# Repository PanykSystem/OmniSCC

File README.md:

# OmniSCC — MSX MultiCart

Current firmware: **2.0.0**. See [release notes — changes since 1.0.0](RELEASE_NOTES.md).

> **Upgrading from 1.0.0:** back up every file on the cartridge before flashing.
> This release changes the flash layout and automatically formats a recognized
> old volume on its first boot. Restore your files afterwards. Install the new
> UF2 and menu ROM together; older menu signatures are no longer recognized.

OmniSCC is an RP2040-based MSX cartridge that loads ROM and floppy disk images
from the Pico's 16 MB flash. It emulates plain and mapped ROM cartridges, the
Konami SCC sound chip, and floppy drives backed by `.dsk` files.

**ROM-game saves:** KUC supports flash saves in a companion `.sav`
for ROMs explicitly named with `[KUC]`, on compatible 16 MiB SPI NOR hardware.
See [KUC setup, capacity and validation status](src/docs/kuc.md).
For an unknown flash profile, both menus accept `kuc_allow_unknown_flash=1`
(default `0`); the hardware requirements still apply. Other cartridge flash,
SRAM and EEPROM profiles remain unsupported. Writable `.dsk` games continue to
save into their disk image.

When powered from USB without the MSX, it appears as a removable drive for
copying images by drag-and-drop. On the MSX, the universal menu browses
files and folders and remembers the last booted image. It automatically uses
SCREEN 1 on MSX1 and SCREEN 5 on recognized MSX2+ BIOS versions with enough VRAM. An alternative menu
provides ten configurable favourites.

*OmniSCC — a 16 MB "purple" Pico clone soldered directly onto the carrier
board.*

---

## Contents of this repository

| Path | What it is |
|------|------------|
| [`firmware/`](firmware/) | Prebuilt firmware images. |
| [`tools/`](tools/) | Menu ROMs, and MSX-DOS utilities. |
| [`src/`](src/) | RP2040 firmware (C11 / C++17) + the Z80 side (`msx/preloader.asm`, `msx/loader.asm`, `msx/loader_fav.asm`). See [`src/README.md`](src/README.md). |
| [`board/OmniSCC/`](board/OmniSCC/) | KiCad project for the base board: schematic, PCB, 3D STEP, fabrication ZIP. |
| [`board/OmniSCC+/`](board/OmniSCC+/) | KiCad project for the level-shifted board. |
| [`enclosure/`](enclosure/) | Printable 3MF files for the base and OmniSCC+ cases. |
| [`images/`](images/) | Board photos used by this file. |

Two software git submodules are used, so clone with:

```bash
git clone --recursive https://github.com/RBSC/OmniSCC.git
# or, in an existing clone:
git submodule update --init --recursive
```

---

## Hardware variants

Both boards run the same firmware sources; they differ only in the board header
selected at build time (`-DPICO_BOARD=omniscc` or `omniscc_plus`).

### OmniSCC (base)

*The Pico module is soldered flat against the carrier board along both pin
rows.*

The Pico drives the MSX bus directly at 3.3 V. Fewest parts, lowest cost. Three
3-pole solder jumpers pick what reaches the Pico on GP26–GP28:

| Jumper | Choice | Required setting for this firmware |
|--------|--------|------------------------------------|
| `IORQ` / `AUDIO` | GP26 | **AUDIO** — GP26 is the SCC PDM audio output. |
| `BUSDIR` / `M1` | GP27 | **BUSDIR** — the firmware never reads `/M1`. |
| `WAIT` / `INT` | GP28 | **WAIT** — the loader stretches every bus cycle with `/WAIT`. |

### OmniSCC+

*OmniSCC+ — same Pico module, plus SN74LVC8T245 bus transceivers for
proper 5 V level translation.*

Address, data and control lines run through level shifters, so the MSX sees
real 5 V logic. There are no option jumpers: GP26 is AUDIO, GP27 is the data
transceiver direction (`DATA_DIR`), GP28 is `/WAIT`. Build with
`-DPICO_BOARD=omniscc_plus`, which defines `WITH_SHIFTERS`.

---

Current [OmniSCC+ hardware revision 1.1](board/OmniSCC+/README.md) adds a
10 kΩ pull-up on `/RES` to address resets in USB mode when touching the connector.
Use the 1.1 fabrication archive for new boards.

## Quick start

1. **Flash the firmware.** Hold **BOOTSEL**, plug into USB, release; copy a
   `.uf2` to the `RPI-RP2` drive. Pre-built images live in
   [`firmware/`](firmware/) — `OmniSCC.uf2` for the base board,
   `OmniSCC+.uf2` for OmniSCC+. To build your own, see
   [`src/README.md`](src/README.md).
2. **Fill the drive.** Plug the cart into USB with the MSX powered off. A
   removable drive named `OmniSCC` appears (the first boot formats the flash and
   writes `WELCOME.TXT`). Copy [`tools/loader.rom`](tools/loader.rom)
   and your `.rom` files to its root. Keep only one `loader*.rom` in the root. To build the menu yourself, see
   [`src/README.md`](src/README.md).
3. **Nothing to configure.** The menu lists what is on the drive and writes
   `/loader.ini` itself when you boot something. Write it by hand only to set a
   countdown or a title before the first boot:

   ```ini
   delay=3000
   scc_on_exit=1
   scc_volume=100
   name=gradius.rom,Gradius
   ```

   For the ten-favourites menu, copy
   [`tools/loader_fav.rom`](tools/loader_fav.rom) to the drive
   **under its original name**. Copy `loader_fav.ini.example` to the drive as
   `loader_fav.ini`, then edit its `favN=` entries to match your files.
   Keep only one `loader*.rom` in the root; see
   [`src/README.md`](src/README.md#which-menu-rom-to-copy).
4. **Eject, plug into the MSX, power on.** The menu appears; it auto-boots
   whatever you booted last when the countdown runs out.

### Menu keys

| Key | Action |
|-----|--------|
| Cursor up / down | Move the highlight; the list scrolls at the edges |
| Cursor left / right | Page up / page down |
| `RETURN` / `SPACE` | Enter a directory, or boot a file |
| `F1` | Open Help, including the running firmware version |
| `BS` | Up one directory |
| `INS` | Assign the highlighted `.dsk` to drive B; pressing INS again keeps it assigned |
| `DEL` | Clear drive B, regardless of the selected entry |
| `ESC` | Leave the menu for BASIC (maps a bare SCC cartridge first if `scc_on_exit` is non-zero) |

Keyboard input or either joystick port cancels the auto-boot countdown.
Joystick directions navigate, A opens/boots, and B goes back or exits.

### SCC volume

The firmware and menus support a global SCC master level in
`loader.ini` (browser) or `loader_fav.ini` (favourites):

```ini
scc_volume=100
```

Use a decimal percentage from `0` to `100`. The default is `100`, which keeps
the previous output level; `50` halves the signal amplitude and `0` mutes SCC.
This is a linear amplitude control, so half the value need not sound half as
loud. The MSX's built-in PSG is unaffected. Channel volumes programmed by the
game keep their relative levels.

The setting applies to SCC ROM games, disk/Nextor SCC audio and the bare SCC
mode selected on exit. It survives SCC chip resets and cartridge changes.
Each menu reads its own INI at startup; restart the menu after editing it.
Invalid or out-of-range values leave the previous value (initially `100`)
unchanged. The browser preserves the setting when rewriting `loader.ini`;
the favourites menu preserves the other lines when saving volume and `default=`.
Install the matching UF2 and updated menu ROM together to use this option.

In either menu, press **`+` / `-`** to change the level in **10% steps**,
clamped to 0–100%. A centred `SCC Volume: 100%` popup appears only while
adjusting, then disappears after about two seconds. ESC dismisses the popup;
press ESC again to leave the menu. Other navigation keys dismiss it and work
normally. Any adjustment cancels auto-boot. The setting is saved when you boot
an entry or leave the menu (and whenever the browser otherwise saves its INI),
not on every keypress. In favourites, literal `-` now controls volume instead
of acting as the AZERTY shortcut for slot 6; the digit `6` still selects it.

### Floppy drive emulation

The cartridge serves `.dsk` files on its USB volume as floppy drives to the
MSX. Select an image in the browser menu to mount it as drive A; the MSX then
resets and boots through the emulated Disk ROM. Press `INS` on another `.dsk`
first to put it in drive B; `DEL` clears B regardless of the selection. The browser saves that choice as `disk2=` in
`loader.ini`. A diskette icon at the left of the row marks the image assigned to B:.
After INS/DEL, drive B status temporarily replaces the centered F1 Help /
Return Open hint. The next keyboard or joystick input restores the hint. Only folders and the assigned B: image have icons;
ordinary ROM and DSK files use the same plain rows in both modes.
You can also set `disk2=` by hand. Whether B: appears to the MSX
depends on the Disk ROM's own drive count; some dumps advertise only A:.

You must supply your own **16 KB MSX Disk ROM dump**; none is distributed with
this project. Copy it to the USB volume as `disk.rom`, or set `diskrom=<path>`
in `loader.ini` to use a different file. The firmware patches a copy of the
dump in RAM when mounting a disk and leaves the file untouched. A dump must
pass the firmware's validation, so an arbitrary 16 KB ROM will not work.
The following 16 KiB dumps have been tested. External downloads are available
from File-Hunter; verify the MD5 checksum before use:

- [yis805-128r2_disk.rom](https://download.file-hunter.com/System%20ROMs/machines/yamaha/yis805-128r2_disk.rom) — MD5: `814aad415b58cc3f78c7b571512b2006`
- [NATIONALDISK.rom](https://download.file-hunter.com/System%20ROMs/machines/yamaha/NATIONALDISK.rom) — MD5: `86269da485e852d9f581ac27f4ba32ff`

If disk games fail or glitch when another disk interface is installed, see
[freeing RAM with DEL during disk boot](#disk-games-fail-when-other-disk-interfaces-are-present).

Images are **writable**: MSX-DOS and Disk BASIC can save files directly into
the `.dsk` on the cartridge's flash. Set an image file's read-only attribute
on the USB volume to make the emulated disk write protected. `CALL FORMAT`
initializes a 360 KB or 720 KB image on either drive. SCC audio remains
available while a disk is mounted.

The firmware accepts any non-empty image whose size is a multiple of 512
bytes; it does not validate the disk's filesystem or geometry when mounting.
Standard 360 KB and 720 KB images work with the supported Disk ROMs. Other
sizes may mount, but Disk BASIC or MSX-DOS may fail when reading them, and
`CALL FORMAT` supports only the two standard sizes.

After booting a disk, you can change images without rebooting. For example,
`CALL OMOUNT("B:SIDE-B.DSK")` inserts an image into drive B and `CALL OEJECT("B:")`
removes it. `CALL ODISK` reports both drives; `CALL ODIR("GAMES")` lists disk
images on the cartridge's USB volume.

The same outer-volume also supports file management from BASIC:

```basic
CALL ODEL("OLD.DSK")
CALL OCOPY("SOURCE.DSK","BACKUP.DSK")
CALL ONEW("EMPTY.DSK")           ' 720 KiB formatted FAT12 image
CALL ONEW("SINGLE.DSK",360)      ' 360 KiB formatted FAT12 image
```

`ODEL` refuses an image mounted in drive A or B. `OCOPY` and `ONEW` never
overwrite an existing file, and copy transfers preserve every source sector.
New images are empty FAT12 images and are not mounted automatically. Paths are
literal `.dsk` paths on the cartridge volume; subdirectories and spaces are
supported.

The firmware unifies BASIC and DOS command names with the `O` prefix.
The old names are replaced. `tools/OmniSCC.dsk` includes all seven commands
and standard MSX-DOS 1.03 / COMMAND 1.11, requiring 64 KiB RAM.
See [disk contents and system-file provenance](tools/DOS-SYSTEM.md).

The matching MSX-DOS programs are `OMOUNT.COM`, `OEJECT.COM`, `ODISK.COM`,
`ODIR.COM`, `ODEL.COM`, `OCOPY.COM` and `ONEW.COM`; copy them into a DOS image
before use. See the [Disk BASIC command guide](src/README.md#disk-commands-from-basic)
and [MSX-DOS command guide](src/msx/dos/README.md) for syntax, protocol limits
and error handling.

---

Numbered DSK switching uses a held top-row digit `1–9` when the game next
accesses the disk BIOS. Press the game's own disk-check key while holding the
digit. Set `multidisk=0` in `loader.ini` or `loader_fav.ini` to disable it
(default `1`), for example if the game uses digits for its controls.

## Supported mappers

Detected automatically from the ROM contents: plain/linear, Konami (8 KB
pages), Konami SCC, ASCII8, ASCII16. Detection can be overridden by putting
`[Plain]`, `[8kB]`, `[Konami]`, `[KonamiSCC]`, `[SCCI]`, `[SCCPlus]`, `[ASCII8]`, `[ASCII16]` or `[KUC]` in the filename
before the extension. KUC supports up to 8 MiB and can also be selected by a known external database
hash.

Plain/Mirrored ROMs choose their start address from the ROM header, including
48 KiB images starting at `0000h`. `[Normal]` disables mirroring; `[0x0000]`,
`[0x4000]` and `[0x8000]` explicitly select a non-mirrored start address.
`[Mirrored4000]` fixes a mirrored ROM at `4000h`. Generic `[8kB]` is selected
by filename or database and switches all four 8 KiB windows, including `4000h`.
It is distinct from Konami and ASCII8; the instruction heuristic does not select it.

`[SCCI]` and `[SCCPlus]` emulate an expanded 128 KiB SCC-I RAM cartridge.
SCCI starts in compatible SCC mode; SCCPlus starts in enhanced mode for ROM
conversions using `B800h`. `[SCC+]` is an alias for `[SCCPlus]`. Both support
RAM-write modes and the `BFFEh`/`BFFFh` mode register. The ROM image initializes
cartridge RAM, with the unused space filled with `FFh`; changes are volatile.
These types are selected by tag or database, not by the instruction heuristic.

The SCC is emulated on core 1 and rendered as a PDM stream through PIO + DMA on
GPIO 26. A bare SCC cartridge with no ROM can also be mapped from the menu (just 
exit to basic), for software that expects an SCC to be present but supplies its 
own code.

ROMs up to 128 KiB are cached in RAM; larger ones are read directly from their
verified flash pages, without a permanent second copy. Mapper limits are Plain
64 KiB, Konami 256 KiB, Konami SCC 2 MiB, SCC-I/SCCPlus 128 KiB, ASCII8 2 MiB, ASCII16 4 MiB and explicit KUC 8 MiB.
The FAT storage area occupies 15 MiB, less flash-translation overhead.

## Nextor on the shared USB volume

Copy `tools/nextor.rom`, `tools/NEXTOR.SYS` and `tools/COMMAND2.COM` to the
cartridge root, then select `nextor.rom` in the menu. Nextor uses the existing
FAT12/FAT16 volume directly; no HDD image or repartitioning is required.
DOS2 needs at least 128 KiB of mapped MSX RAM. See the
[Nextor guide](src/docs/nextor.md), including `SET EXPERT ON` for COM programs.
The kernel and DOS files are distributed with [their licence](tools/NEXTOR-LICENSE.md).

## Storage recovery

If flash mapping is valid but FAT cannot mount, the cartridge starts USB MSC
for repair or formatting. Connect through USB, repair the existing filesystem
or format FAT12/FAT16, safely eject and restart. Files are not automatically
erased merely because FAT failed to mount.

A damaged or unrecognized flash map is recreated automatically with a fresh
FAT. **That reset loses the previous files.** If flash itself fails, USB still
enumerates but the storage remains not-ready. Install the matching firmware and menu ROM together.

## MSX1 and MSX2 menus

The 16 KiB universal `tools/loader.rom` includes a 32×24 SCREEN 1 interface with
the existing 8×8 font, rounded frame, folder and assigned-disk icons and inverse
selection. It retains the full browser functionality and 16 visible entries.
MSX1 or unknown BIOS versions select this interface; recognized MSX2+ BIOS
versions use SCREEN 5 only after a restoring probe confirms at least 32 KiB VRAM.
A V9938 by itself does not imply MSX2 BIOS or enough VRAM. No separate lite ROM
is required. The optional 16 KiB favourites menu uses the same automatic mode selection, font,
frame and inverse selection, with all ten slots, digit shortcuts, Help and auto-boot.

Both graphical menus show only the centered OmniSCC logo, without a menu subtitle,
while reading configuration
and preparing the menu. With at least 64 KiB VRAM, initialization uses a hidden
page and reveals the completed menu without a partial redraw. The splash adds
no fixed delay; MSX1 text mode and 32 KiB graphics retain the hidden-screen startup.

**Browser — MSX1 (SCREEN 1)**

**Browser — MSX2 (SCREEN 5)**

**Favourites — MSX1 (SCREEN 1)**

**Favourites — MSX2 (SCREEN 5)**

Menu mapper detection uses the exact eight bytes `OmniSCC\0` at ROM offset
`0x10`, independently of the filename. Explicit mapper tags retain priority.
The preloader still searches the root for the first `loader*.rom`; keep only
one such file. Verify release payloads with `sha256sum -c SHA256SUMS` from the
repository root.

---

## ROM mapper database

Copy `tools/romdb.bin` to the cartridge root with the matching menus. Both INI
files accept `romdb=/romdb.bin`; an empty value disables lookup. Filename tags
win, then known hashes, then the instruction heuristic. Matched tags are hidden
in both menus. See [database generation and custom hashes](src/docs/rom-database.md).

## Troubleshooting

### Older SCC+ ROM conversions hang or play only PSG

Select enhanced SCC+ mode with `[SCCPlus]` or `[SCC+]` in the filename; `[SCCI]`
starts in compatible SCC mode. Some older Konami Game Collection conversions
also contain loader bugs: bank switching with Z80 interrupts enabled, or reliance
on Disk ROM RAM-slot variables before those variables have been initialized.
Such images can work in one emulator configuration and fail on another machine
or boot differently after a reset.

Use a corrected conversion if the mapper is selected correctly but the game
still hangs or its music fails. The
[conversion loader fixes](https://www.msx.org/forum/msx-talk/general-discussion/konami-game-collection-roms-patches)
describe these issues. Changing SCC volume does not repair the game's loader.

### Disk games fail when other disk interfaces are present

Each initialized Disk ROM can reserve MSX RAM for its drives and disk buffers.
If the machine already has another Disk ROM and drives, adding OmniSCC's disk
interface can sharply reduce free RAM. A disk game may then fail to start,
hang or behave incorrectly even though the same image works with fewer disk
interfaces.

On computers with built-in disk drives, try holding **CTRL** immediately after
starting a DSK image in the OmniSCC menu. Keep it held through the restart and
initial disk boot. On Disk ROMs that support this option, CTRL disables the
second logical floppy drive and reduces disk-buffer memory usage, leaving more
RAM for the game. The effect depends on the machine and Disk ROM.

For the supported **Yamaha YIS805 Disk ROM** (`yis805-128r2_disk.rom`),
use the following boot procedure:

1. Select the `.dsk` image in the OmniSCC menu.
2. Press **Enter**, then immediately press and hold **CTRL**.
3. Keep **CTRL held until the game has finished loading**.

Hold CTRL during the restart and disk boot, not just while the menu is visible.
This is a Disk ROM boot option; its behavior can differ with another Disk ROM
or machine.

On some models, holding **DEL** during startup disables the built-in network
BIOS and can free additional RAM for disk games. This is a separate,
machine-specific boot option.

### ROM games fail after a warm reset

If a ROM game does not start from the OmniSCC menu after a reset, switch the
computer off for **at least 10 seconds**, then switch it on and try again.
A warm reset may leave RAM or peripheral state that affects the next launch;
a full power cycle gives the machine and cartridge a fresh startup.

---

## Enclosure

[`enclosure/`](enclosure/) contains ready-to-print `OmniSCC.3MF` (base board)
and `OmniSCC+.3mf` (level-shifted board). `carts.3mf` is also
included.
Fill free to remove non required parts in the slicer.

---

## Documentation

- [`src/README.md`](src/README.md) — building, flashing, `loader.ini`
  reference, mapper tags, troubleshooting.
- [`src/docs/omniscc_api.md`](src/docs/omniscc_api.md) — the Z80↔Pico
  command protocol, for writing your own MSX-side software.

---

## IMPORTANT!
The RBSC provides all the files and information for free, without any liability. 
The provided information, software or hardware must not be used for commercial purposes unless permitted by the RBSC.
Producing a small amount of bare boards for personal projects and selling the rest of the batch is allowed without the permission of RBSC.
When the sources of the tools are used to create alternative projects, please always mention the original source and the copyright!

---

## Contact information

The members of RBSC group Tnt23, Wierzbowsky, Pyhesty, Ptero, GreyWolf, SuperMax, VWarlock, ALSP and DJS3000 can be
contacted via the group's e-mail address:

info@rbsc.su

The group's coordinator could be reached via this e-mail address:

admin@rbsc.su

The group's website can be found here:

https://rbsc.su/
https://rbsc.su/ru

The RBSC's hardware repository can be found here:

https://github.com/rbsc

The RBSC's 3D model repository can be found here:

https://www.thingiverse.com/groups/rbsc/things

-= ! MSX FOREVER ! =-

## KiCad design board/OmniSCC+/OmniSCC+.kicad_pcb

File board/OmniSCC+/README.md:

# OmniSCC+ — level-shifted board

KiCad 8 project for OmniSCC+: the same 16 MB Raspberry Pi Pico clone, but with
SN74LVC8T245 bus transceivers between the RP2040 and the MSX slot, so the MSX
sees proper 5 V logic levels on the address, data and control lines.

## Revision 1.1

R7 (10 kΩ, 0805) pulls `/RES` up to `+5VA`. This hardware change addresses
spontaneous resets observed in USB mode when touching the connector on revision
1.0. Use the revision 1.1 PCB and fabrication archive for new boards.

## USB stability fix for revision 1.0

Revision 1.0 has no pull-up resistor on `/RES`. The floating reset signal can
cause spontaneous resets in USB mode, for example when touching the USB
connector. Add a **10 kΩ resistor between `/RES` and `+5VA`** to retrofit the
pull-up included as R7 on revision 1.1.

1. Disconnect the board from both the MSX and USB before soldering.
2. With the board oriented as in the picture, solder the 10 kΩ resistor and
   connecting wire between the two marked points. The resistor has no polarity.
3. Insulate the resistor lead and wire where needed so they cannot short to
   neighbouring pads or the cartridge edge contacts. Check the solder joints
   and reconnect USB to verify stable operation.

This is a hardware modification; changing the firmware alone does not add the
pull-up. Revision 1.1 already includes R7 and needs no additional resistor.

## Files

| File | Contents |
|------|----------|
| `OmniSCC+.kicad_sch` / `.kicad_pcb` / `.kicad_pro` | Schematic, layout, project |
| `production/OmniSCCplus_1_1_Gerber.zip` | Revision 1.1 Gerbers and drill files (no BOM/CPL) |
| `production/netlist.ipc` | Revision 1.1 IPC-D-356 netlist for electrical test |
| `fabrication-toolkit-options.json` | KiCad Fabrication Toolkit settings used to generate the ZIP |
| `Datasheets/OmniSCC+-v1.0-schematic.pdf` | Historical revision 1.0 schematic; use the KiCad schematic for 1.1 |
| `Datasheets/RPPICOPURPLE-pin-1024x438.jpg` | Pinout of the 16 MB Pico clone |
| `../../LICENSE` | Project license |

The old `production/OmniSCCplus_1_0_Gerber.zip` and `production/v1.0/` assembly
CSVs are retained for revision 1.0 only. They must not be used to assemble 1.1:
component positions changed and R7 was added. Generate new assembly exports
from the revision 1.1 KiCad project when needed.

Symbols and footprints come from the OSPC library
([OSPC_Library](https://github.com/VWarlock/OSPC_Library)); configure it before
opening the project.

## Differences from the base board

- Level shifters on the whole bus instead of a direct 3.3 V connection.
- No option jumpers. GP26 is `AUDIO`, GP27 is the data transceiver direction
  (`DATA_DIR`), GP28 is `/WAIT`. `/IORQ`, `/BUSDIR`, `/M1` and `/INT` are not
  routed to the RP2040.

Build the firmware for this board with `-DPICO_BOARD=omniscc_plus`, which
defines `WITH_SHIFTERS`.

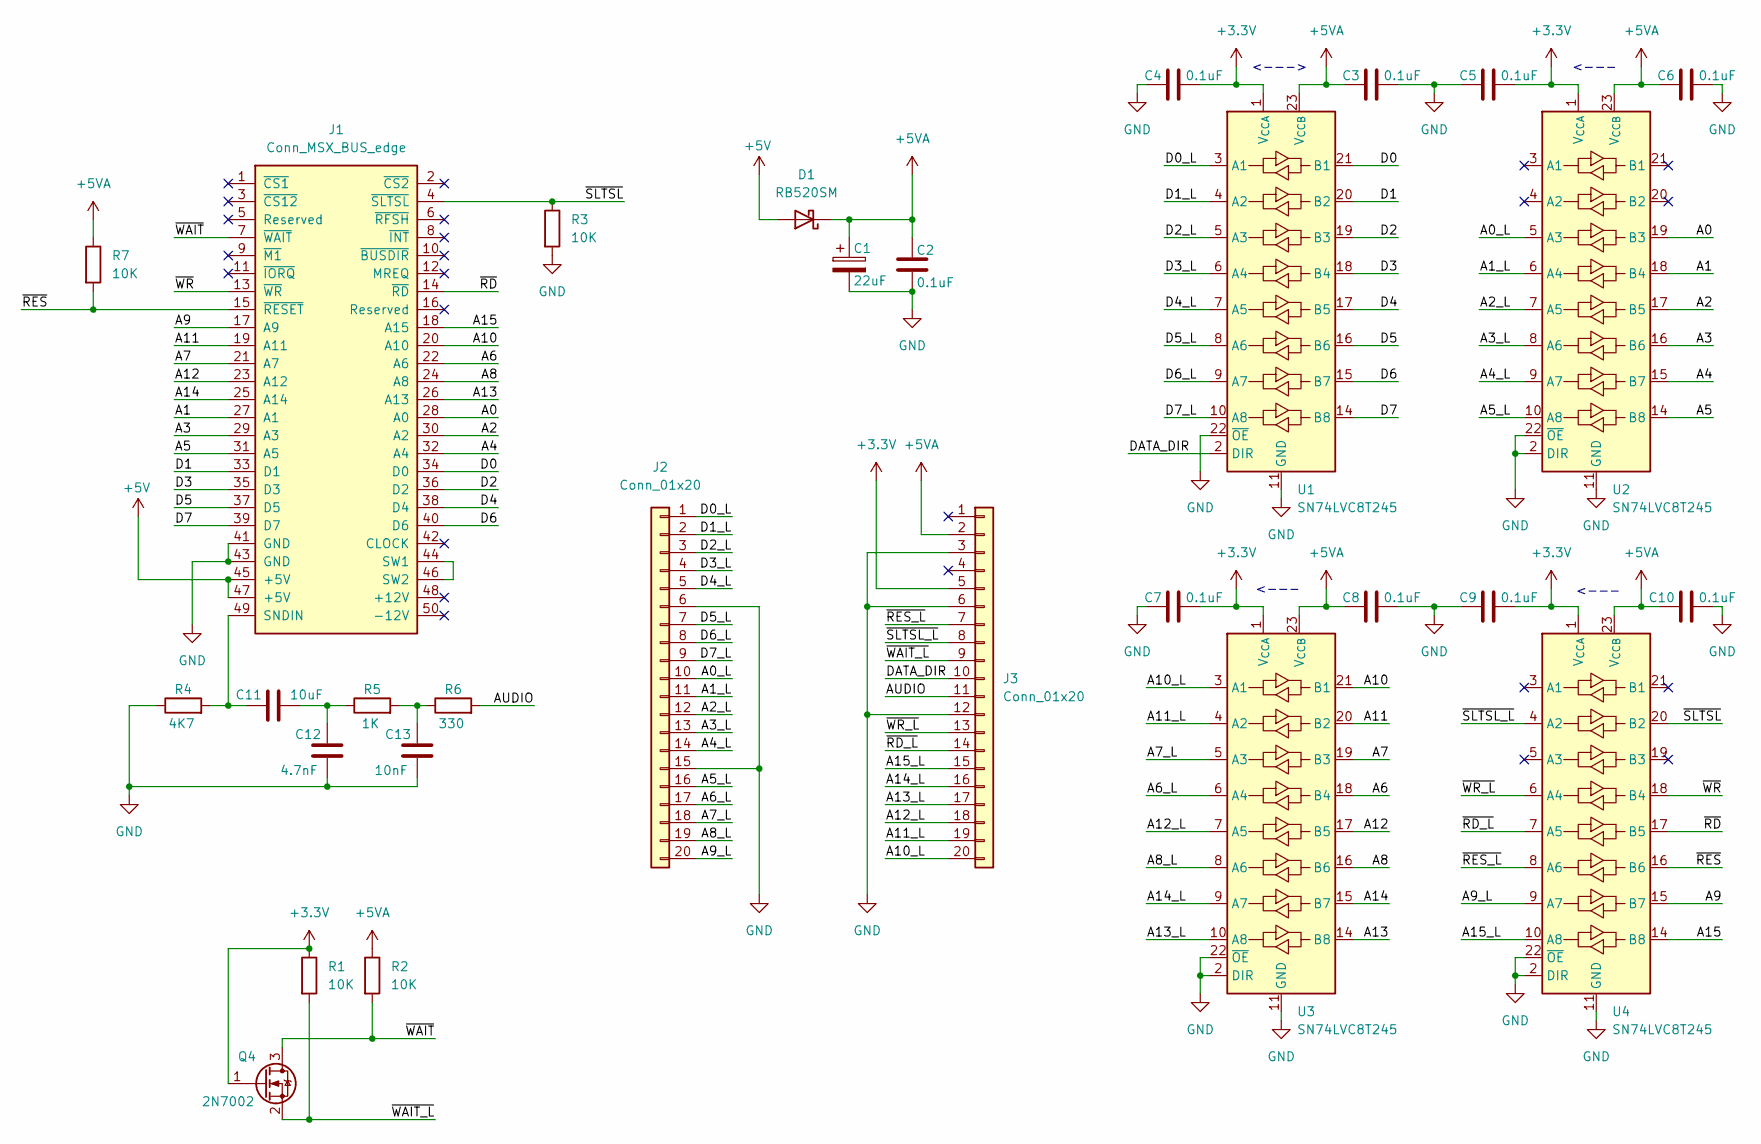
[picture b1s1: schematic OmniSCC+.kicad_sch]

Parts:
C1: 22uF; CP_EIA-3528-21_Kemet-B
C2, C3, C4, C5, C6, C7, C8, C9, C10: 0.1uF; C_0805_2012Metric
C11: 10uF; C_0805_2012Metric
C12: 4.7nF; C_0805_2012Metric
C13: 10nF; C_0805_2012Metric
D1: RB520SM; D_SOD-123; JLCPCB C8523
J1: Conn_MSX_BUS_edge; MSX_CART_SW_Small
J2, J3: Conn_01x20; PinSocket_1x20_P2.54mm_Vertical
Q4: 2N7002; SOT-23; LCSC C8545
R1, R2, R3, R7: 10K; R_0805_2012Metric_Pad1.20x1.40mm_HandSolder
R4: 4K7; R_0805_2012Metric
R5: 1K; R_0805_2012Metric
R6: 330; R_0805_2012Metric
U1, U2, U3, U4: SN74LVC8T245; TSSOP-24_4.4x7.8mm_P0.65mm

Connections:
+3.3V: C4.2, C5.2, C7.2, C9.2, J3.5, Q4.1 (G), R1.1, U1.1 (V_{CCA}), U2.1 (V_{CCA}), U3.1 (V_{CCA}), U4.1 (V_{CCA})
+5V: D1.2 (A), J1.45 (+5V), J1.47 (+5V)
+5VA: C1.1, C2.1, C3.1, C6.1, C8.1, C10.1, D1.1 (K), J3.2, R2.1, R7.1, U1.23 (V_{CCB}), U1.24 (V_{CCB}), U2.23 (V_{CCB}), U2.24 (V_{CCB}), U3.23 (V_{CCB}), U3.24 (V_{CCB}), U4.23 (V_{CCB}), U4.24 (V_{CCB})
/A0: J1.28 (A0), U2.19 (B3)
/A0_L: J2.10, U2.5 (A3)
/A1: J1.27 (A1), U2.18 (B4)
/A1_L: J2.11, U2.6 (A4)
/A2: J1.30 (A2), U2.17 (B5)
/A2_L: J2.12, U2.7 (A5)
/A3: J1.29 (A3), U2.16 (B6)
/A3_L: J2.13, U2.8 (A6)
/A4: J1.32 (A4), U2.15 (B7)
/A4_L: J2.14, U2.9 (A7)
/A5: J1.31 (A5), U2.14 (B8)
/A5_L: J2.16, U2.10 (A8)
/A6: J1.22 (A6), U3.18 (B4)
/A6_L: J2.17, U3.6 (A4)
/A7: J1.21 (A7), U3.19 (B3)
/A7_L: J2.18, U3.5 (A3)
/A8: J1.24 (A8), U3.16 (B6)
/A8_L: J2.19, U3.8 (A6)
/A9: J1.17 (A9), U4.15 (B7)
/A9_L: J2.20, U4.9 (A7)
/A10: J1.20 (A10), U3.21 (B1)
/A10_L: J3.20, U3.3 (A1)
/A11: J1.19 (A11), U3.20 (B2)
/A11_L: J3.19, U3.4 (A2)
/A12: J1.23 (A12), U3.17 (B5)
/A12_L: J3.18, U3.7 (A5)
/A13: J1.26 (A13), U3.14 (B8)
/A13_L: J3.17, U3.10 (A8)
/A14: J1.25 (A14), U3.15 (B7)
/A14_L: J3.16, U3.9 (A7)
/A15: J1.18 (A15), U4.14 (B8)
/A15_L: J3.15, U4.10 (A8)
/AUDIO: J3.11, R6.2
/D0: J1.34 (D0), U1.21 (B1)
/D0_L: J2.1, U1.3 (A1)
/D1: J1.33 (D1), U1.20 (B2)
/D1_L: J2.2, U1.4 (A2)
/D2: J1.36 (D2), U1.19 (B3)
/D2_L: J2.3, U1.5 (A3)
/D3: J1.35 (D3), U1.18 (B4)
/D3_L: J2.4, U1.6 (A4)
/D4: J1.38 (D4), U1.17 (B5)
/D4_L: J2.5, U1.7 (A5)
/D5: J1.37 (D5), U1.16 (B6)
/D5_L: J2.7, U1.8 (A6)
/D6: J1.40 (D6), U1.15 (B7)
/D6_L: J2.8, U1.9 (A7)
/D7: J1.39 (D7), U1.14 (B8)
/D7_L: J2.9, U1.10 (A8)
/DATA_DIR: J3.10, U1.2 (DIR)
/~RD_L: J3.14, U4.7 (A5)
/~RD: J1.14 (~RD), U4.17 (B5)
/~RES_L: J3.7, U4.8 (A6)
/~RES: J1.15 (~RESET), R7.2, U4.16 (B6)
/~SLTSL_L: J3.8, U4.4 (A2)
/~SLTSL: J1.4 (~SLTSL), R3.1, U4.20 (B2)
/~WAIT_L: J3.9, Q4.2 (S), R1.2
/~WAIT: J1.7 (~WAIT), Q4.3 (D), R2.2
/~WR_L: J3.13, U4.6 (A4)
/~WR: J1.13 (~WR), U4.18 (B4)
GND: C1.2, C2.2, C3.2, C4.1, C5.1, C6.2, C7.1, C8.2, C9.1, C10.2, C12.1, C13.1, J1.41 (GND), J1.43 (GND), J2.6, J2.15, J3.3, J3.6, J3.12, R3.2, R4.1, U1.11 (GND), U1.12 (GND), U1.13 (GND), U1.22 (~OE), U2.2 (DIR), U2.11 (GND), U2.12 (GND), U2.13 (GND), U2.22 (~OE), U3.2 (DIR), U3.11 (GND), U3.12 (GND), U3.13 (GND), U3.22 (~OE), U4.2 (DIR), U4.11 (GND), U4.12 (GND), U4.13 (GND), U4.22 (~OE)
unnamed: C11.2, C12.2, R5.1
unnamed: C13.2, R5.2, R6.1
unnamed: C11.1, J1.49 (SNDIN), R4.2
unnamed: J1.44 (SW1), J1.46 (SW2)

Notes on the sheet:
<---
<--->

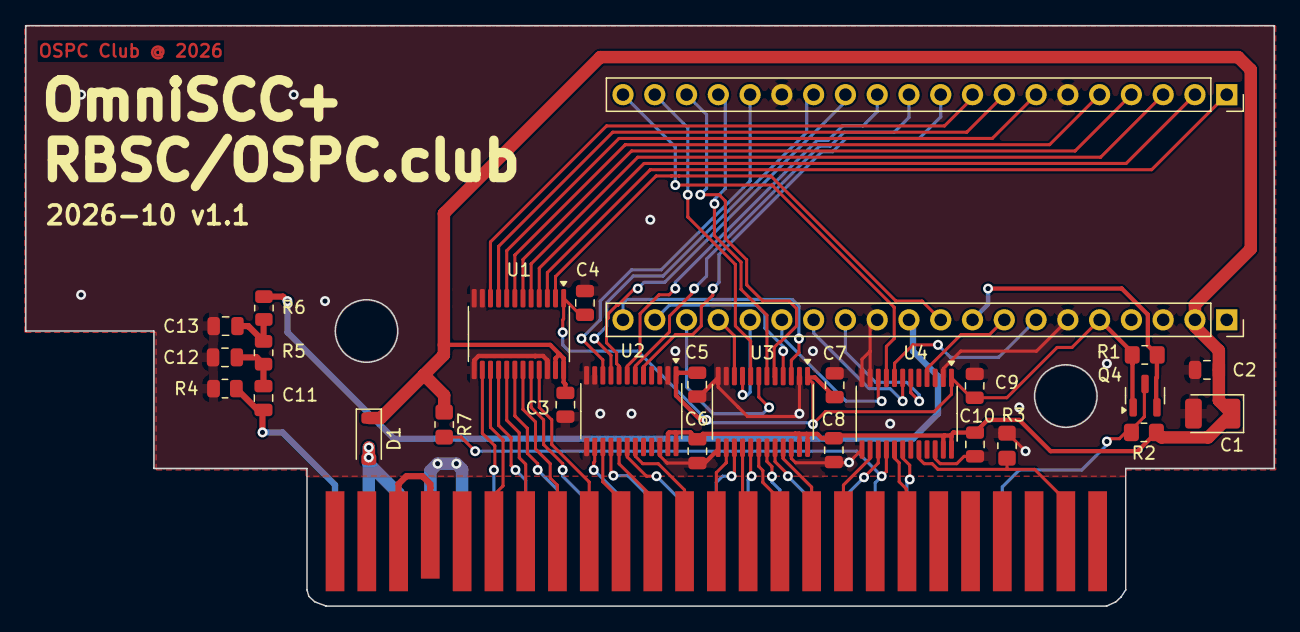
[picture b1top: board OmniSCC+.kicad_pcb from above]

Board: 2 copper layers, 99.8 x 46.4 mm, 29 parts (0 on the bottom side), 68 nets.

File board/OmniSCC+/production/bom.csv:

Designator,Footprint,Quantity,Value,LCSC Part #
C1,CP_EIA-3528-21_Kemet-B,1,22uF,
"C10, C2, C3, C4, C5, C6, C7, C8, C9",0805,9,0.1uF,
C11,0805,1,10uF,
C12,0805,1,4.7nF,
C13,0805,1,10nF,
D1,D_SOD-123,1,RB520SM,
J1,MSX_CART_SW_Small,1,Conn_MSX_BUS_edge,
"J2, J3",PinSocket_1x20_P2.54mm_Vertical,2,Conn_01x20,
Q4,SOT-23,1,2N7002,C8545
"R1, R2, R3",0805,3,10K,
R4,0805,1,4K7,
R5,0805,1,1K,
R6,0805,1,330,
"U1, U2, U3, U4",TSSOP-24_4.4x7.8mm_P0.65mm,4,SN74LVC8T245,

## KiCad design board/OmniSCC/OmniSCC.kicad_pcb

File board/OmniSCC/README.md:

# OmniSCC — base board

KiCad 8 project for the base OmniSCC carrier: a 16 MB "purple" Raspberry Pi
Pico clone soldered flat onto an MSX cartridge edge connector, with no level
translation — the RP2040 drives the MSX bus directly at 3.3 V.

## Files

| File | Contents |
|------|----------|
| `OmniSCC.kicad_sch` / `.kicad_pcb` / `.kicad_pro` | Schematic, layout, project |
| `3D/OmniSCC.step` | 3D model of the assembled board |
| `production/OmniSCC_1.0.zip` | Gerbers + drill + BOM/CPL for fabrication |
| `production/netlist.ipc` | IPC-D-356 netlist for electrical test |
| `Datasheets/OmniSCC-v1.0.pdf` | Schematic as PDF |
| `Datasheets/RPPICOPURPLE-pin-1024x438.jpg` | Pinout of the 16 MB Pico clone |

Symbols and footprints come from the `Board/libs` submodule
([OSPC_Library](https://github.com/VWarlock/OSPC_Library)); initialise it before
opening the project.

## Option jumpers

Three 3-pole solder jumpers choose what reaches GP26–GP28. The firmware in
[`firmware/`](../../firmware/) expects:

| Jumper | Selects | Set to |
|--------|---------|--------|
| `IORQ` / `AUDIO` | GP26 | **AUDIO** — SCC PDM audio output |
| `BUSDIR` / `M1` | GP27 | **BUSDIR** — `/M1` is unused |
| `WAIT` / `INT` | GP28 | **WAIT** — the loader stretches bus cycles |

Build the firmware for this board with `-DPICO_BOARD=omniscc` (the default).

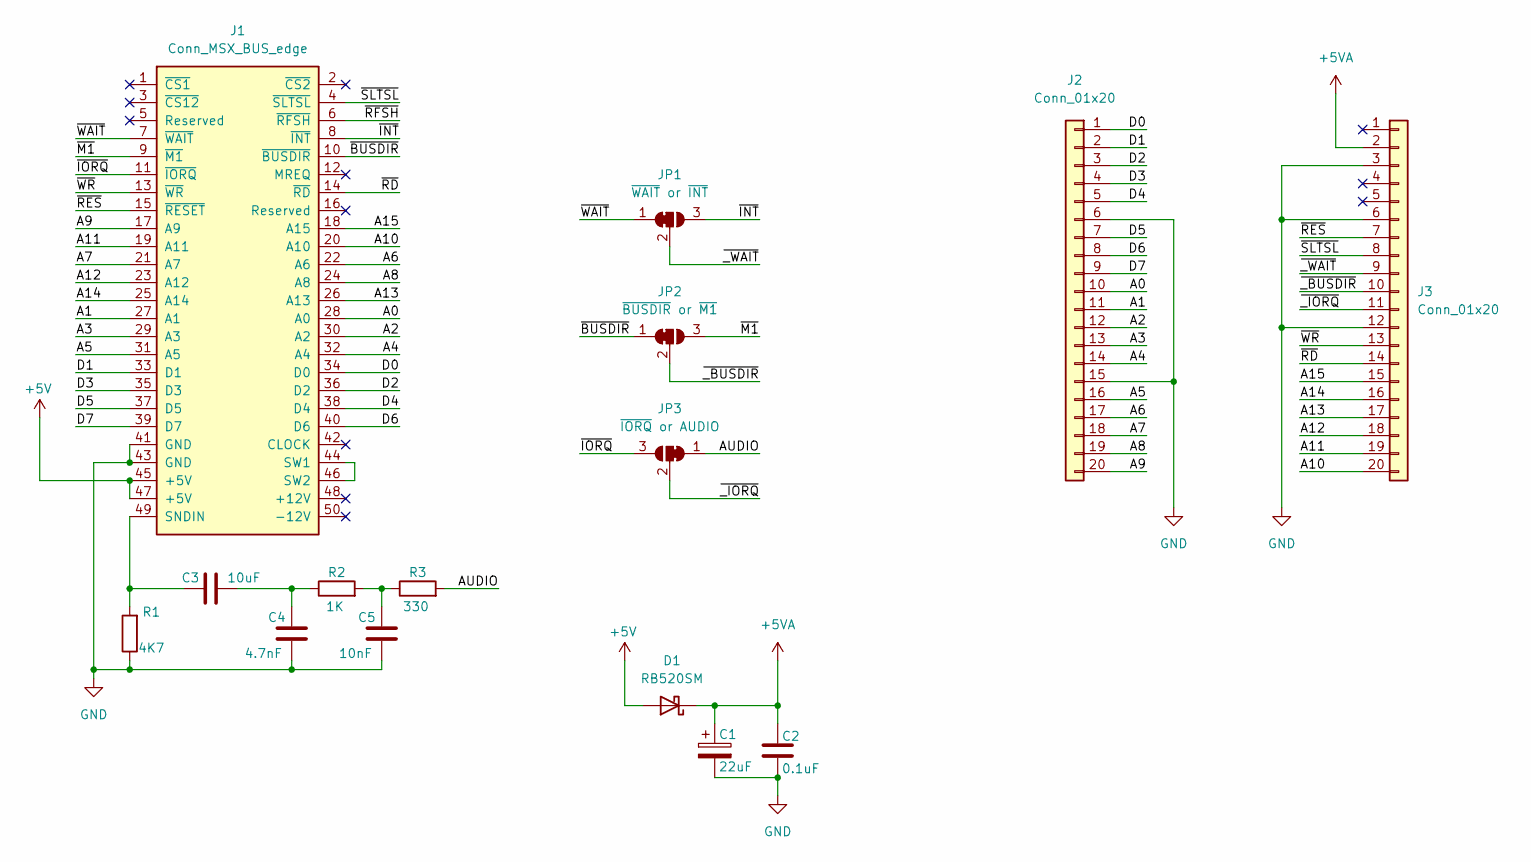
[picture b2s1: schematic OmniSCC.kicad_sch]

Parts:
C1: 22uF; CP_EIA-3528-21_Kemet-B
C2: 0.1uF; C_0805_2012Metric
C3: 10uF; C_0805_2012Metric
C4: 4.7nF; C_0805_2012Metric
C5: 10nF; C_0805_2012Metric
D1: RB520SM; D_SOD-123; JLCPCB C8523
J1: Conn_MSX_BUS_edge; MSX_CART_SW_Official
J2, J3: Conn_01x20; PinSocket_1x20_P2.54mm_Vertical
JP1: ~{WAIT} or ~{INT}; SolderJumper-3_P1.3mm_Bridged12_RoundedPad1.0x1.5mm_NumberL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
JP2: ~{BUSDIR} or ~{M1}; SolderJumper-3_P1.3mm_Bridged12_RoundedPad1.0x1.5mm_NumberL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
JP3: ~{IORQ} or AUDIO; SolderJumper-3_P1.3mm_Bridged12_RoundedPad1.0x1.5mm_NumberL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
R1: 4K7; R_0805_2012Metric
R2: 1K; R_0805_2012Metric
R3: 330; R_0805_2012Metric

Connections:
+5V: D1.2 (A), J1.45 (+5V), J1.47 (+5V)
+5VA: C1.1, C2.1, D1.1 (K), J3.2
/A0: J1.28 (A0), J2.10
/A1: J1.27 (A1), J2.11
/A2: J1.30 (A2), J2.12
/A3: J1.29 (A3), J2.13
/A4: J1.32 (A4), J2.14
/A5: J1.31 (A5), J2.16
/A6: J1.22 (A6), J2.17
/A7: J1.21 (A7), J2.18
/A8: J1.24 (A8), J2.19
/A9: J1.17 (A9), J2.20
/A10: J1.20 (A10), J3.20
/A11: J1.19 (A11), J3.19
/A12: J1.23 (A12), J3.18
/A13: J1.26 (A13), J3.17
/A14: J1.25 (A14), J3.16
/A15: J1.18 (A15), J3.15
/AUDIO: JP3.1 (A), R3.2
/D0: J1.34 (D0), J2.1
/D1: J1.33 (D1), J2.2
/D2: J1.36 (D2), J2.3
/D3: J1.35 (D3), J2.4
/D4: J1.38 (D4), J2.5
/D5: J1.37 (D5), J2.7
/D6: J1.40 (D6), J2.8
/D7: J1.39 (D7), J2.9
/~BUSDIR: J1.10 (~BUSDIR), JP2.1 (A)
/~INT: J1.8 (~INT), JP1.3 (B)
/~IORQ: J1.11 (~IORQ), JP3.3 (B)
/~M1: J1.9 (~M1), JP2.3 (B)
/~RD: J1.14 (~RD), J3.14
/~RES: J1.15 (~RESET), J3.7
/~RFSH: J1.6 (~RFSH)
/~SLTSL: J1.4 (~SLTSL), J3.8
/~WAIT: J1.7 (~WAIT), JP1.1 (A)
/~WR: J1.13 (~WR), J3.13
/~_BUSDIR: J3.10, JP2.2 (C)
/~_IORQ: J3.11, JP3.2 (C)
/~_WAIT: J3.9, JP1.2 (C)
GND: C1.2, C2.2, C4.1, C5.1, J1.41 (GND), J1.43 (GND), J2.6, J2.15, J3.3, J3.6, J3.12, R1.1
unnamed: C3.2, C4.2, R2.1
unnamed: C5.2, R2.2, R3.1
unnamed: C3.1, J1.49 (SNDIN), R1.2
unnamed: J1.44 (SW1), J1.46 (SW2)

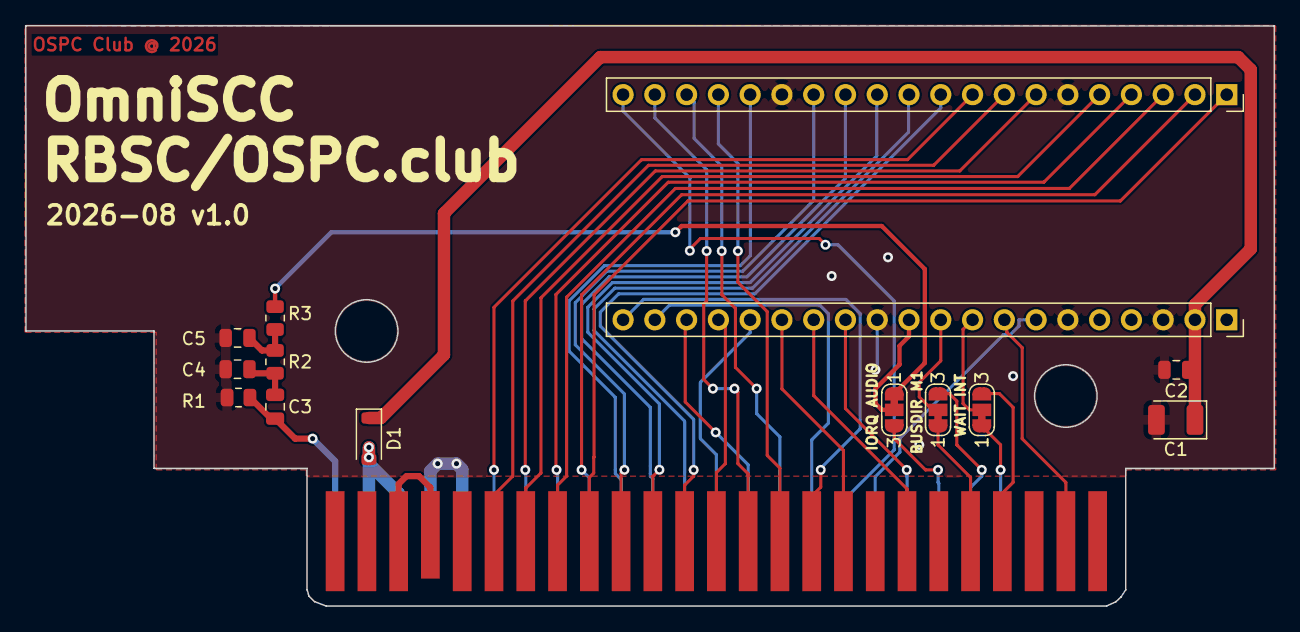
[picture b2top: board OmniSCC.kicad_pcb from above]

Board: 2 copper layers, 99.8 x 46.4 mm, 15 parts (0 on the bottom side), 44 nets.

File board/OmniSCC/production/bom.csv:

Designator,Footprint,Quantity,Value,LCSC Part #
C1,CP_EIA-3528-21_Kemet-B,1,22uF,
C2,0805,1,0.1uF,
C3,0805,1,10uF,
C4,0805,1,4.7nF,
C5,0805,1,10nF,
D1,D_SOD-123,1,RB520SM,
J1,MSX_CART_SW_Official,1,Conn_MSX_BUS_edge,
"J2, J3",PinSocket_1x20_P2.54mm_Vertical,2,Conn_01x20,
R1,0805,1,4K7,
R2,0805,1,1K,
R3,0805,1,330,
